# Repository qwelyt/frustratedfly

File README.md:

# FrustratedFly
A 38-key angled colstagger keybeard using Kailh cpg1316s switches and a rp2040-zero for brains.

# Libraries used
For cpg1316s: https://github.com/mikeholscher/zmk-config-mikefive/tree/main/files/footprint-and-cad
For rp2040-Zero 3d model: https://github.com/crides/kleeb/blob/master/models/rp2040-zero.step

Put the step files in the `kicad-libraries` folder and you should get a good 3d-view.

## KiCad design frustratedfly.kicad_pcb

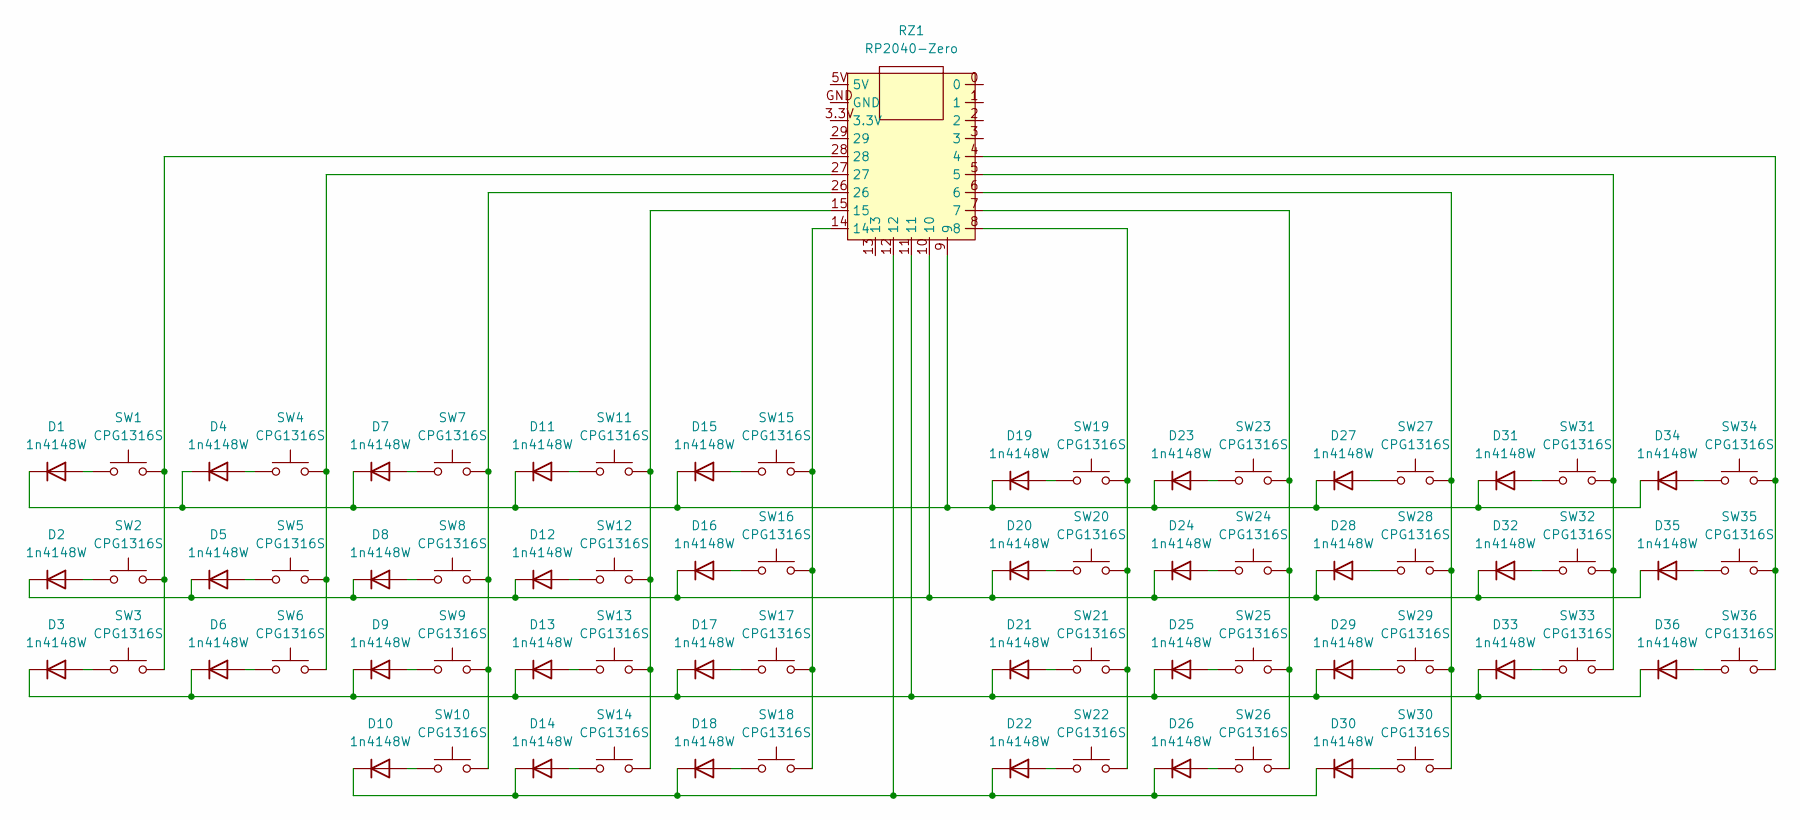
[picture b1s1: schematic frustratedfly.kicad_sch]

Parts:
D1, D2, D3, D4, D5, D6, D7, D8, D9, D10, D11, D12, D13, D14, D15, D16, D17, D18, D19, D20, D21, D22, D23, D24, D25, D26, D27, D28, D29, D30, D31, D32, D33, D34, D35, D36: 1n4148W; D_SOD-123; LCSC Part # C2099
RZ1: RP2040-Zero; RP2040_Zero_cutout
SW1, SW2, SW3, SW4, SW5, SW6, SW7, SW8, SW9, SW10, SW11, SW12, SW13, SW14, SW15, SW16, SW17, SW18, SW19, SW20, SW21, SW22, SW23, SW24, SW25, SW26, SW27, SW28, SW29, SW30, SW31, SW32, SW33, SW34, SW35, SW36: CPG1316S; CPG1316S01D02_mikeholscher_w_ref; LCSC Part # C42372112

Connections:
unnamed: D1.2 (A), SW1.1
unnamed: D1.1 (K), D4.1 (K), D7.1 (K), D11.1 (K), D15.1 (K), D19.1 (K), D23.1 (K), D27.1 (K), D31.1 (K), D34.1 (K), RZ1.9
unnamed: D2.2 (A), SW2.1
unnamed: D3.2 (A), SW3.1
unnamed: D4.2 (A), SW4.1
unnamed: D5.2 (A), SW5.1
unnamed: D6.2 (A), SW6.1
unnamed: D7.2 (A), SW7.1
unnamed: D8.2 (A), SW8.1
unnamed: D9.2 (A), SW9.1
unnamed: D10.2 (A), SW10.1
unnamed: D10.1 (K), D14.1 (K), D18.1 (K), D22.1 (K), D26.1 (K), D30.1 (K), RZ1.12
unnamed: D11.2 (A), SW11.1
unnamed: D12.2 (A), SW12.1
unnamed: D2.1 (K), D5.1 (K), D8.1 (K), D12.1 (K), D16.1 (K), D20.1 (K), D24.1 (K), D28.1 (K), D32.1 (K), D35.1 (K), RZ1.10
unnamed: D13.2 (A), SW13.1
unnamed: D3.1 (K), D6.1 (K), D9.1 (K), D13.1 (K), D17.1 (K), D21.1 (K), D25.1 (K), D29.1 (K), D33.1 (K), D36.1 (K), RZ1.11
unnamed: D14.2 (A), SW14.1
unnamed: D15.2 (A), SW15.1
unnamed: D16.2 (A), SW16.1
unnamed: D17.2 (A), SW17.1
unnamed: D18.2 (A), SW18.1
unnamed: D19.2 (A), SW19.1
unnamed: D20.2 (A), SW20.1
unnamed: D21.2 (A), SW21.1
unnamed: D22.2 (A), SW22.1
unnamed: D23.2 (A), SW23.1
unnamed: D24.2 (A), SW24.1
unnamed: D25.2 (A), SW25.1
unnamed: D26.2 (A), SW26.1
unnamed: D27.2 (A), SW27.1
unnamed: D28.2 (A), SW28.1
unnamed: D29.2 (A), SW29.1
unnamed: D30.2 (A), SW30.1
unnamed: D31.2 (A), SW31.1
unnamed: D32.2 (A), SW32.1
unnamed: D33.2 (A), SW33.1
unnamed: D34.2 (A), SW34.1
unnamed: D35.2 (A), SW35.1
unnamed: D36.2 (A), SW36.1
unnamed: RZ1.4, SW34.2, SW35.2, SW36.2
unnamed: RZ1.5, SW31.2, SW32.2, SW33.2
unnamed: RZ1.6, SW27.2, SW28.2, SW29.2, SW30.2
unnamed: RZ1.7, SW23.2, SW24.2, SW25.2, SW26.2
unnamed: RZ1.8, SW19.2, SW20.2, SW21.2, SW22.2
unnamed: RZ1.14, SW15.2, SW16.2, SW17.2, SW18.2
unnamed: RZ1.15, SW11.2, SW12.2, SW13.2, SW14.2
unnamed: RZ1.26, SW7.2, SW8.2, SW9.2, SW10.2
unnamed: RZ1.27, SW4.2, SW5.2, SW6.2
unnamed: RZ1.28, SW1.2, SW2.2, SW3.2

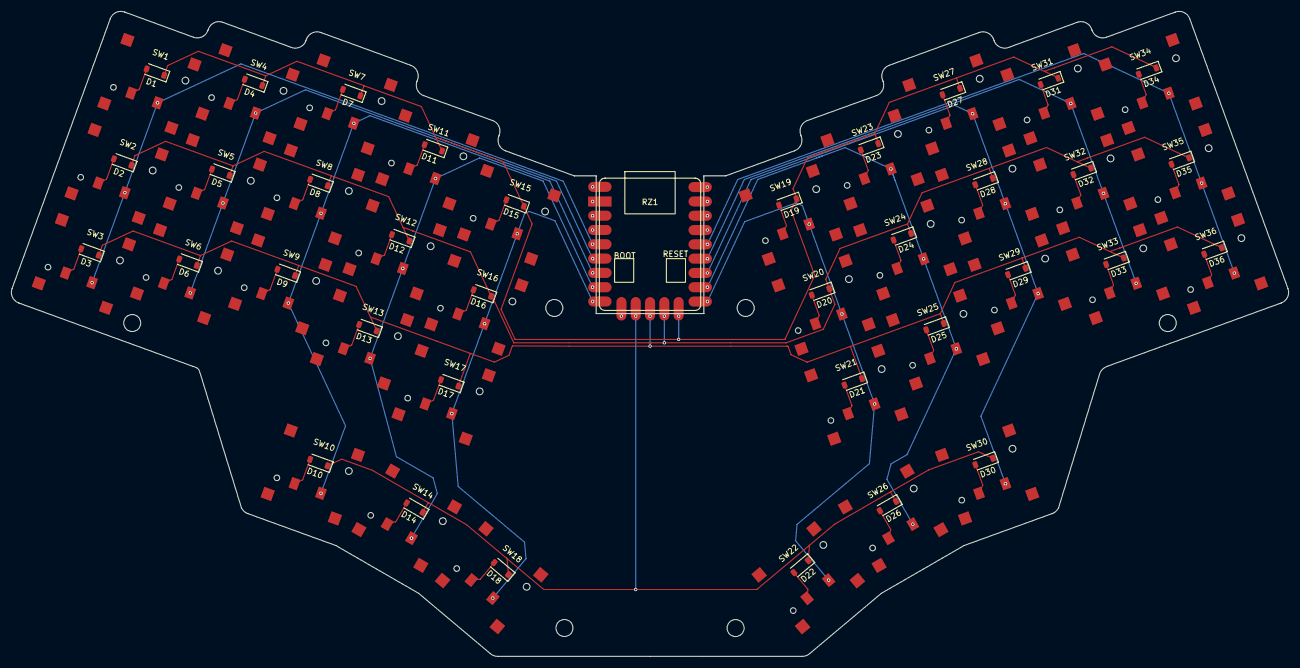
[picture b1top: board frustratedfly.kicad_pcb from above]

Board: 2 copper layers, 226.8 x 114.5 mm, 73 parts (0 on the bottom side), 50 nets.

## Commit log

2025-05-14 Update ignore
2025-05-14 Add the project
2025-05-14 Added project specific kicad libs
2025-06-04 17mm ctc spacing
